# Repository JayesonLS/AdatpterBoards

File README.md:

# AdatpterBoards
Various designs for adapter boards. Unless otherwise specificed, 
these designes are all placed into the Public Domain. See LICENSE
for more details.

Battery BR-2/3A to CR2032
-------------------------

**STATUS:** Untested.

Allows use of a CR2032 in place of a Panasonic BR-2/3A, as used
in some PS/2's for example.

Interposer 486 3V
-----------------

**STATUS:** Untested. Assembling will be complicated - instructions to follow. 

Allows a 3V 486 CPU to be used on mainboards with only 5V CPU support.
Jumpers allow selection of:

* CLKMUL selection supported by some CPUs.
* Selecting between write-back or write-through cache.
  Not all CPUs or motherboards support write-back cache.
* CPU voltage of 3.3v or 3.45v.

5V power to the interposer board can be provided externally, or, through the
otherwise unused outer ring of pins available on Socket 2 and Socket 3.

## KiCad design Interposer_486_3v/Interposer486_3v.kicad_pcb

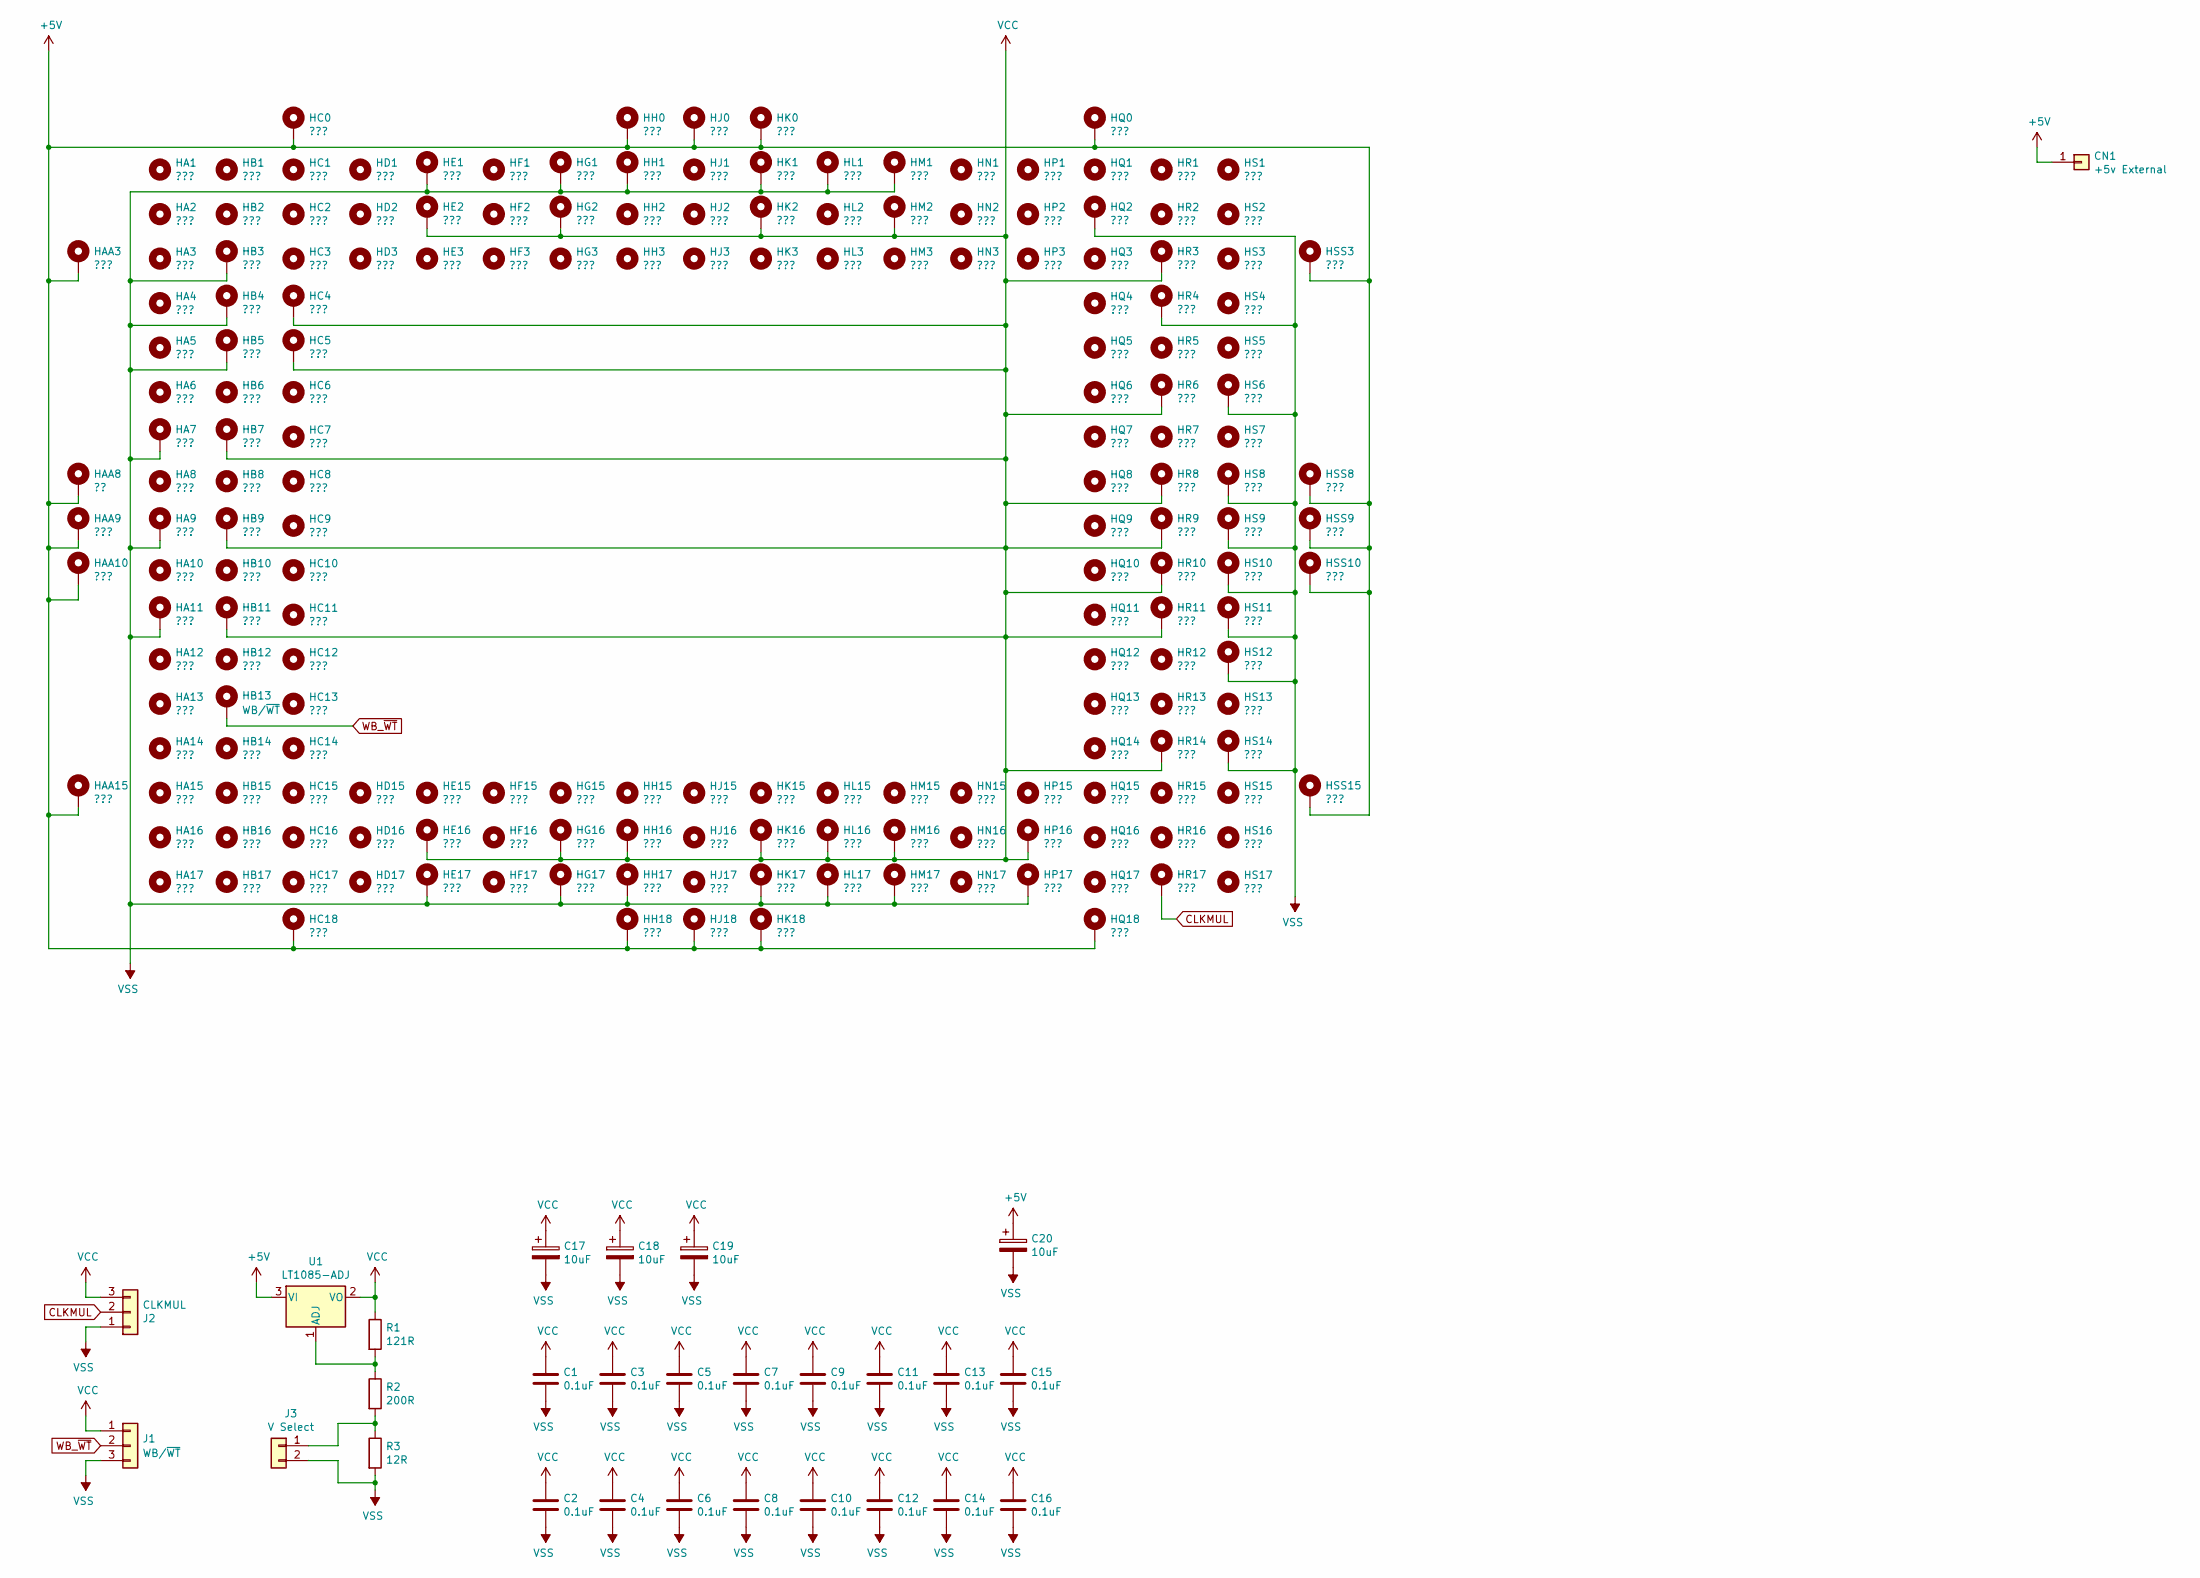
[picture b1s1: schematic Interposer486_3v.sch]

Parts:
C1, C2, C3, C4, C5, C6, C7, C8, C9, C10, C11, C12, C13, C14, C15, C16: 0.1uF; C_1206_3216Metric
C17, C18, C19, C20: 10uF; CP_EIA-3216-10_Kemet-I
CN1: +5v External; SolderWirePad_1x01_SMD_1x2mm
HA1, HA2, HA3, HA4, HA5, HA6, HA7, HA8, HA9, HA10, HA11, HA12, HA13, HA14, HA15, HA16, HA17: ???; MachinePinHole
HAA3, HAA9, HAA10, HAA15: ???; MachinePinHole
HAA8: ??; MachinePinHole
HB1, HB2, HB3, HB4, HB5, HB6, HB8, HB10, HB12, HB14, HB15, HB16, HB17: ???; MachinePinHole
HB7, HB9, HB11: ???; MachinePinHoleHighlighted
HB13: WB/~WT; MachinePinHoleHighlighted
HC0, HC1, HC2, HC3, HC6, HC7, HC8, HC9, HC10, HC11, HC12, HC13, HC14, HC15, HC16, HC17, HC18: ???; MachinePinHole
HC4, HC5: ???; MachinePinHoleHighlighted
HD1, HD2, HD3, HD15, HD16, HD17: ???; MachinePinHole
HE1, HE3, HE15, HE17: ???; MachinePinHole
HE2, HE16: ???; MachinePinHoleHighlighted
HF1, HF2, HF3, HF15, HF16, HF17: ???; MachinePinHole
HG1, HG3, HG15, HG17: ???; MachinePinHole
HG2, HG16: ???; MachinePinHoleHighlighted
HH0, HH1, HH2, HH3, HH15, HH17, HH18: ???; MachinePinHole
HH16: ???; MachinePinHoleHighlighted
HJ0, HJ1, HJ2, HJ3, HJ15, HJ16, HJ17, HJ18: ???; MachinePinHole
HK0, HK1, HK3, HK15, HK17, HK18: ???; MachinePinHole
HK2, HK16: ???; MachinePinHoleHighlighted
HL1, HL2, HL3, HL15, HL17: ???; MachinePinHole
HL16: ???; MachinePinHoleHighlighted
HM1, HM3, HM15, HM17: ???; MachinePinHole
HM2, HM16: ???; MachinePinHoleHighlighted
HN1, HN2, HN3, HN15, HN16, HN17: ???; MachinePinHole
HP1, HP2, HP3, HP15, HP17: ???; MachinePinHole
HP16: ???; MachinePinHoleHighlighted
HQ0, HQ1, HQ2, HQ3, HQ4, HQ5, HQ6, HQ7, HQ8, HQ9, HQ10, HQ11, HQ12, HQ13, HQ14, HQ15, HQ16, HQ17, HQ18: ???; MachinePinHole
HR1, HR2, HR4, HR5, HR7, HR12, HR13, HR15, HR16: ???; MachinePinHole
HR3, HR6, HR8, HR9, HR10, HR11, HR14, HR17: ???; MachinePinHoleHighlighted
HS1, HS2, HS3, HS4, HS5, HS6, HS7, HS8, HS9, HS10, HS11, HS12, HS13, HS14, HS15, HS16, HS17: ???; MachinePinHole
HSS3, HSS8, HSS9, HSS10, HSS15: ???; MachinePinHole
J1: WB/~WT; PinHeader_1x03_P2.54mm_Vertical_SMD_Pin1Left
J2: CLKMUL; PinHeader_1x03_P2.54mm_Vertical_SMD_Pin1Left
J3: V Select; PinHeader_1x02_P2.54mm_Vertical_SMD_Pin1Left
R1: 121R; R_1206_3216Metric
R2: 200R; R_1206_3216Metric
R3: 12R; R_1206_3216Metric
U1: LT1085-ADJ; TO-263-3_TabPin2

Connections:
+5V: C20.1, CN1.1, HAA3.1, HAA8.1, HAA9.1, HAA10.1, HAA15.1, HC0.1, HC18.1, HH0.1, HH18.1, HJ0.1, HJ18.1, HK0.1, HK18.1, HQ0.1, HQ18.1, HSS3.1, HSS8.1, HSS9.1, HSS10.1, HSS15.1, U1.3 (VI)
CLKMUL: HR17.1, J2.2
unnamed: J3.1, R2.2, R3.1
unnamed: R1.2, R2.1, U1.1 (ADJ)
VCC: C1.1, C2.1, C3.1, C4.1, C5.1, C6.1, C7.1, C8.1, C9.1, C10.1, C11.1, C12.1, C13.1, C14.1, C15.1, C16.1, C17.1, C18.1, C19.1, HB7.1, HB9.1, HB11.1, HC4.1, HC5.1, HE2.1, HE16.1, HG2.1, HG16.1, HH16.1, HK2.1, HK16.1, HL16.1, HM2.1, HM16.1, HP16.1, HR3.1, HR6.1, HR8.1, HR9.1, HR10.1, HR11.1, HR14.1, J1.1, J2.3, R1.1, U1.2 (VO)
VSS: C1.2, C2.2, C3.2, C4.2, C5.2, C6.2, C7.2, C8.2, C9.2, C10.2, C11.2, C12.2, C13.2, C14.2, C15.2, C16.2, C17.2, C18.2, C19.2, C20.2, HA7.1, HA9.1, HA11.1, HB3.1, HB4.1, HB5.1, HE1.1, HE17.1, HG1.1, HG17.1, HH1.1, HH17.1, HK1.1, HK17.1, HL1.1, HL17.1, HM1.1, HM17.1, HP17.1, HQ2.1, HR4.1, HS6.1, HS8.1, HS9.1, HS10.1, HS11.1, HS12.1, HS14.1, J1.3, J2.1, J3.2, R3.2
WB_~WT: HB13.1, J1.2

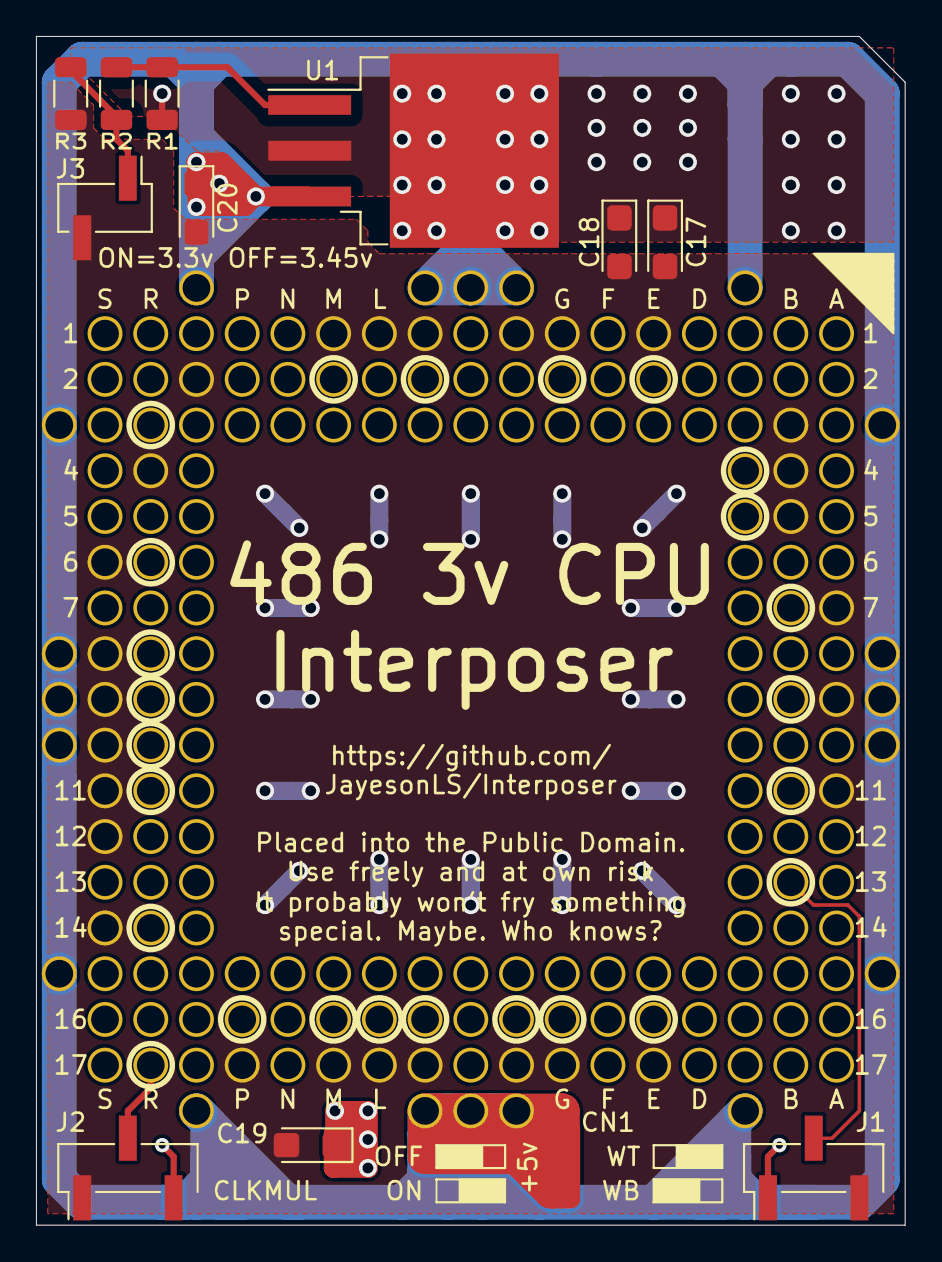
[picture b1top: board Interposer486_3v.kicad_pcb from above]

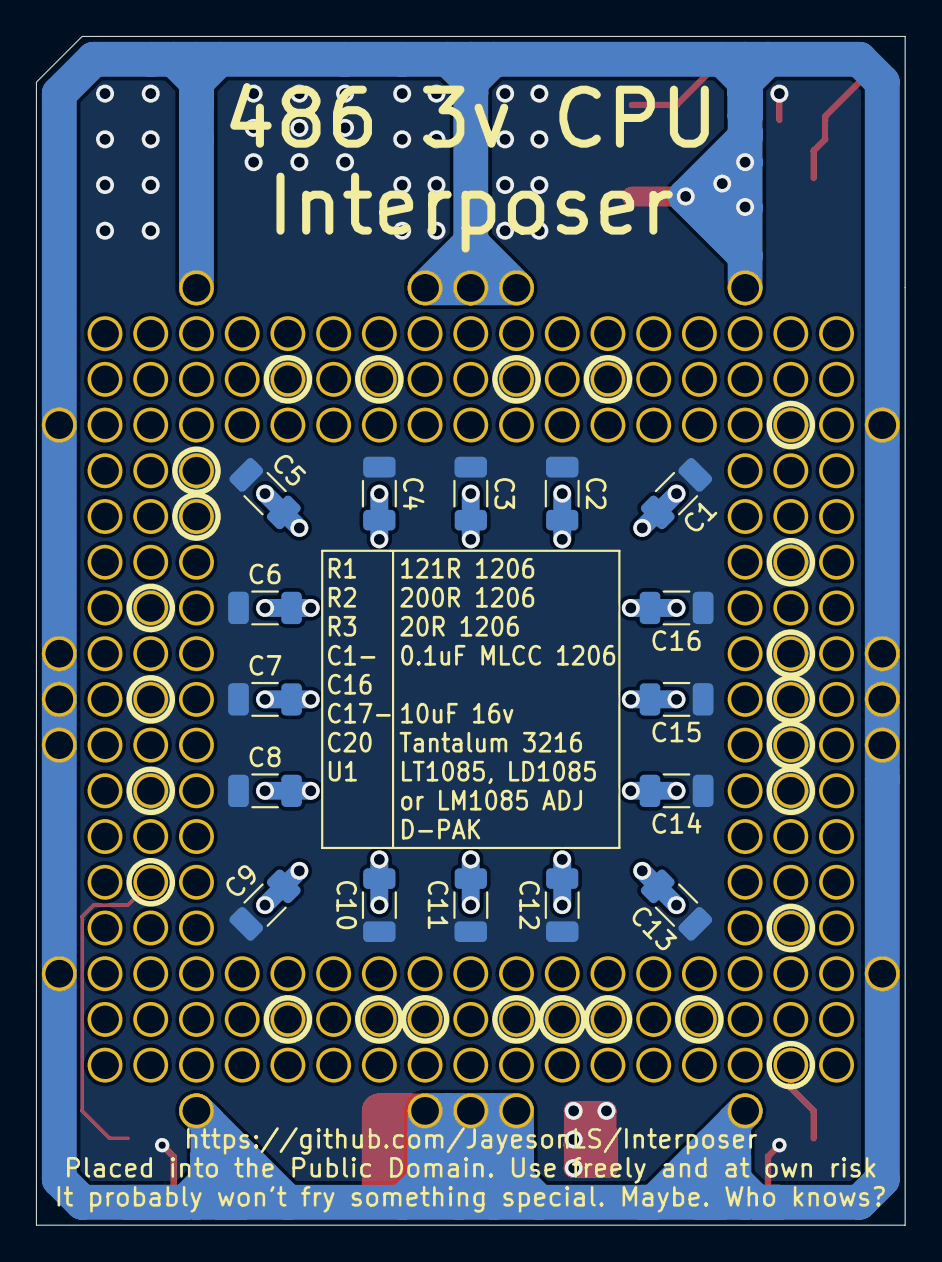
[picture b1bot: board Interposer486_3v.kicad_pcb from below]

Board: 2 copper layers, 48.3 x 66.0 mm, 216 parts (16 on the bottom side), 7 nets.

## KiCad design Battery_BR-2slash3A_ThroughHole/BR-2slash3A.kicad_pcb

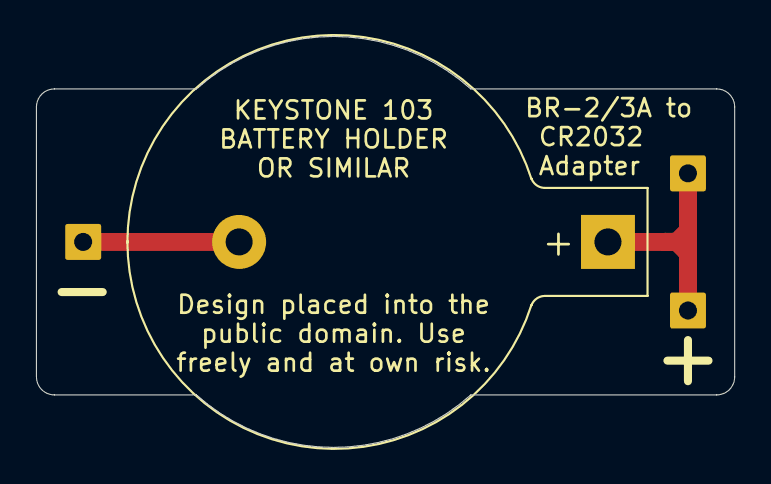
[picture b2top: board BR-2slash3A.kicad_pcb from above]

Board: 2 copper layers, 38.8 x 22.8 mm, 4 parts (0 on the bottom side), 2 nets.

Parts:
BT1: Battery_Cell; BatteryHolder_Keystone_103_1x20mm
H1, H2: Pos; SolderWire-1.5sqmm_1x01_D1.7mm_OD3.9mm
H3: Neg; SolderWire-1.5sqmm_1x01_D1.7mm_OD3.9mm

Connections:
unnamed: BT1.1, H1.1, H2.1
unnamed: BT1.2, H3.1

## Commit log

2021-07-28 Initial commit of 486 3v interposer.
2021-07-28 Completed first pass of layout of 486 3v interposer.
2021-07-29 Jig hole wip
2021-07-30 Add license (public domain).
2021-07-30 Finished first pass of 486 3v interposer.
2021-07-31 Rename Interposer_486_3v folder.
2021-07-31 Add BR-2/3A to CR2032 adapter boards.
2021-07-31 Add gerbers for Interposer 486 3v.
2021-07-31 Add board images.
2021-09-15 Remove drill template from 486 3v interposer.

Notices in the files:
Battery_BR-2slash3A_ThroughHole/BR-2slash3A.kicad_pcb:
Design placed into the
public domain. Use
Interposer_486_3v/Interposer486_3v.kicad_pcb:
Placed into the Public Domain. Use freely and at own risk
